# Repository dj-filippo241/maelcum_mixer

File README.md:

# Maelcum Mixer

A one-off, fully analogue, modular dub performance mixer for a 5-way sound system.

Musical decisions and panel layout: Filippo. Engineering (topologies, simulations, PCB generation): Claude, under Filippo's review.

**Status.** Nothing has been built or measured on a bench yet. Every circuit number comes from LTspice simulation or from Python models. The musical behaviour (control laws, saturators, filter character) is being validated by ear on a Max for Live prototype. Component purchases are on hold until that prototype is complete. The PCBs are generated drafts.

## Start here

- **Technical dossier (English):** [`docs/dossier-en/maelcum-mixer-dossier.pdf`](docs/dossier-en/maelcum-mixer-dossier.pdf), also as [HTML](docs/dossier-en/dossier.html). It is the complete English entry point: architecture, every module, numbers and their sources.
- **Block diagrams (English):** [`docs/diagrammi/en/`](docs/diagrammi/en/index.html), starting from [`schema-totale.svg`](docs/diagrammi/en/schema-totale.svg).

The rest of the repository is written in Italian. Technical terms stay in English where they are standard (headroom, summing, feedback, taper).

## Architecture in one paragraph

Four DJ channels (CDJ/line, optional MM phono) with a 4-band isolator EQ and a VCA fader. A shared global filter (HPF and LPF buses after the fader, Xone:96-style law, OTA core with overdrive). A 5-way performance EQ / dub preamp with a kill per band, matching the crossover of the sound system. Four FX buses with a 16-VCA feedback matrix. Mic and generic mono modules. Master, booth and record outputs, CUE, metering in six zones. Design targets: 0 dBu nominal, system headroom of at least +24 dBu (master clips at about +25.5 dBu), no automatic dynamics, nonlinearity only where intended. Simulated system noise: about -83 dBu A-weighted with filters off.

## Repository map

| Path | Content |
|---|---|
| `SPECIFICA.md` | Consolidated specification |
| `docs/01-decisioni-bloccate.md` | Locked decisions, with date and origin |
| `docs/02-questioni-aperte.md` | Open questions |
| `docs/fase1/` ... `docs/fase4/` | Design documents per module |
| `sim/` | LTspice netlists (`.cir`) and results (`RISULTATI-*.md`); shared models in `sim/lib/` |
| `pcb/` | KiCad schematics and 4-layer PCBs, generated by `pcb/<module>/<module>.py` with `pcb/tools/pcbgen.py` |
| `proto-max/` | Max for Live prototype: generators and tests in `proto-max/coefficienti/` |
| `docs/pannelli/` | Panel renders |
| `cheap/` | A parallel low-cost variant, on hold |

Status tags used in the documents: BLOCCATO (locked), PROVVISORIO (provisional), APERTO (open), SUPERATO (superseded, kept as an alternative or as evidence of a dead end).

## Tools

- LTspice 26.0.2, run in batch with `sim/run_ltspice.sh <netlist.cir>`.
- KiCad 10.0.7 with Freerouting; boards are regenerated from their Python script, never edited by hand.
- Max for Live (gen~) for the prototype; the `.genexpr`, `.maxpat` and `.amxd` files are generated.

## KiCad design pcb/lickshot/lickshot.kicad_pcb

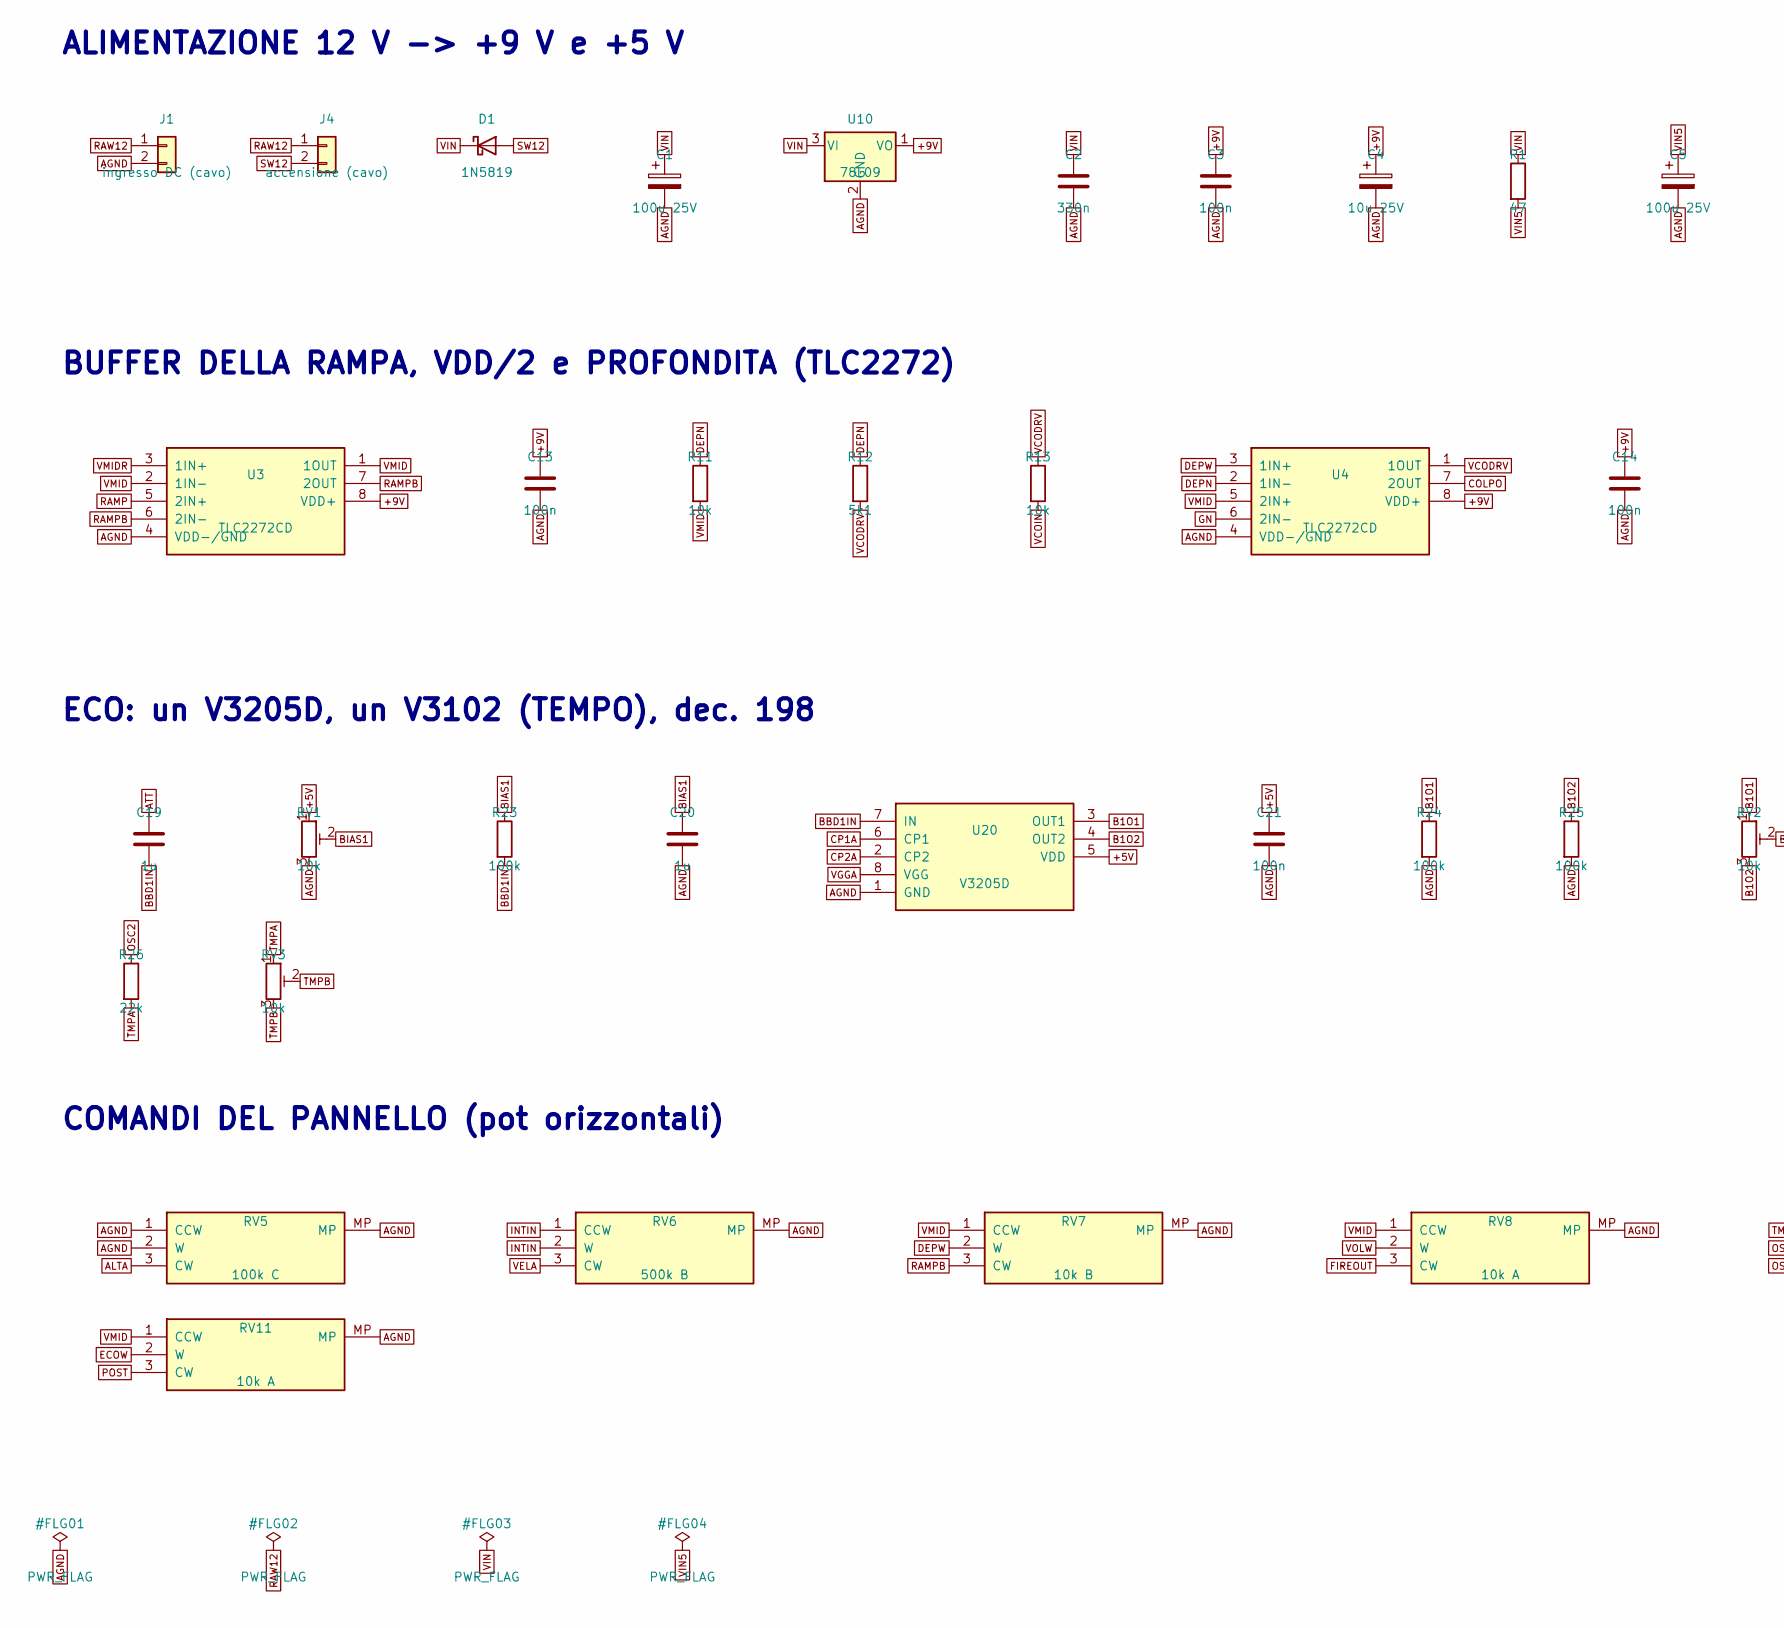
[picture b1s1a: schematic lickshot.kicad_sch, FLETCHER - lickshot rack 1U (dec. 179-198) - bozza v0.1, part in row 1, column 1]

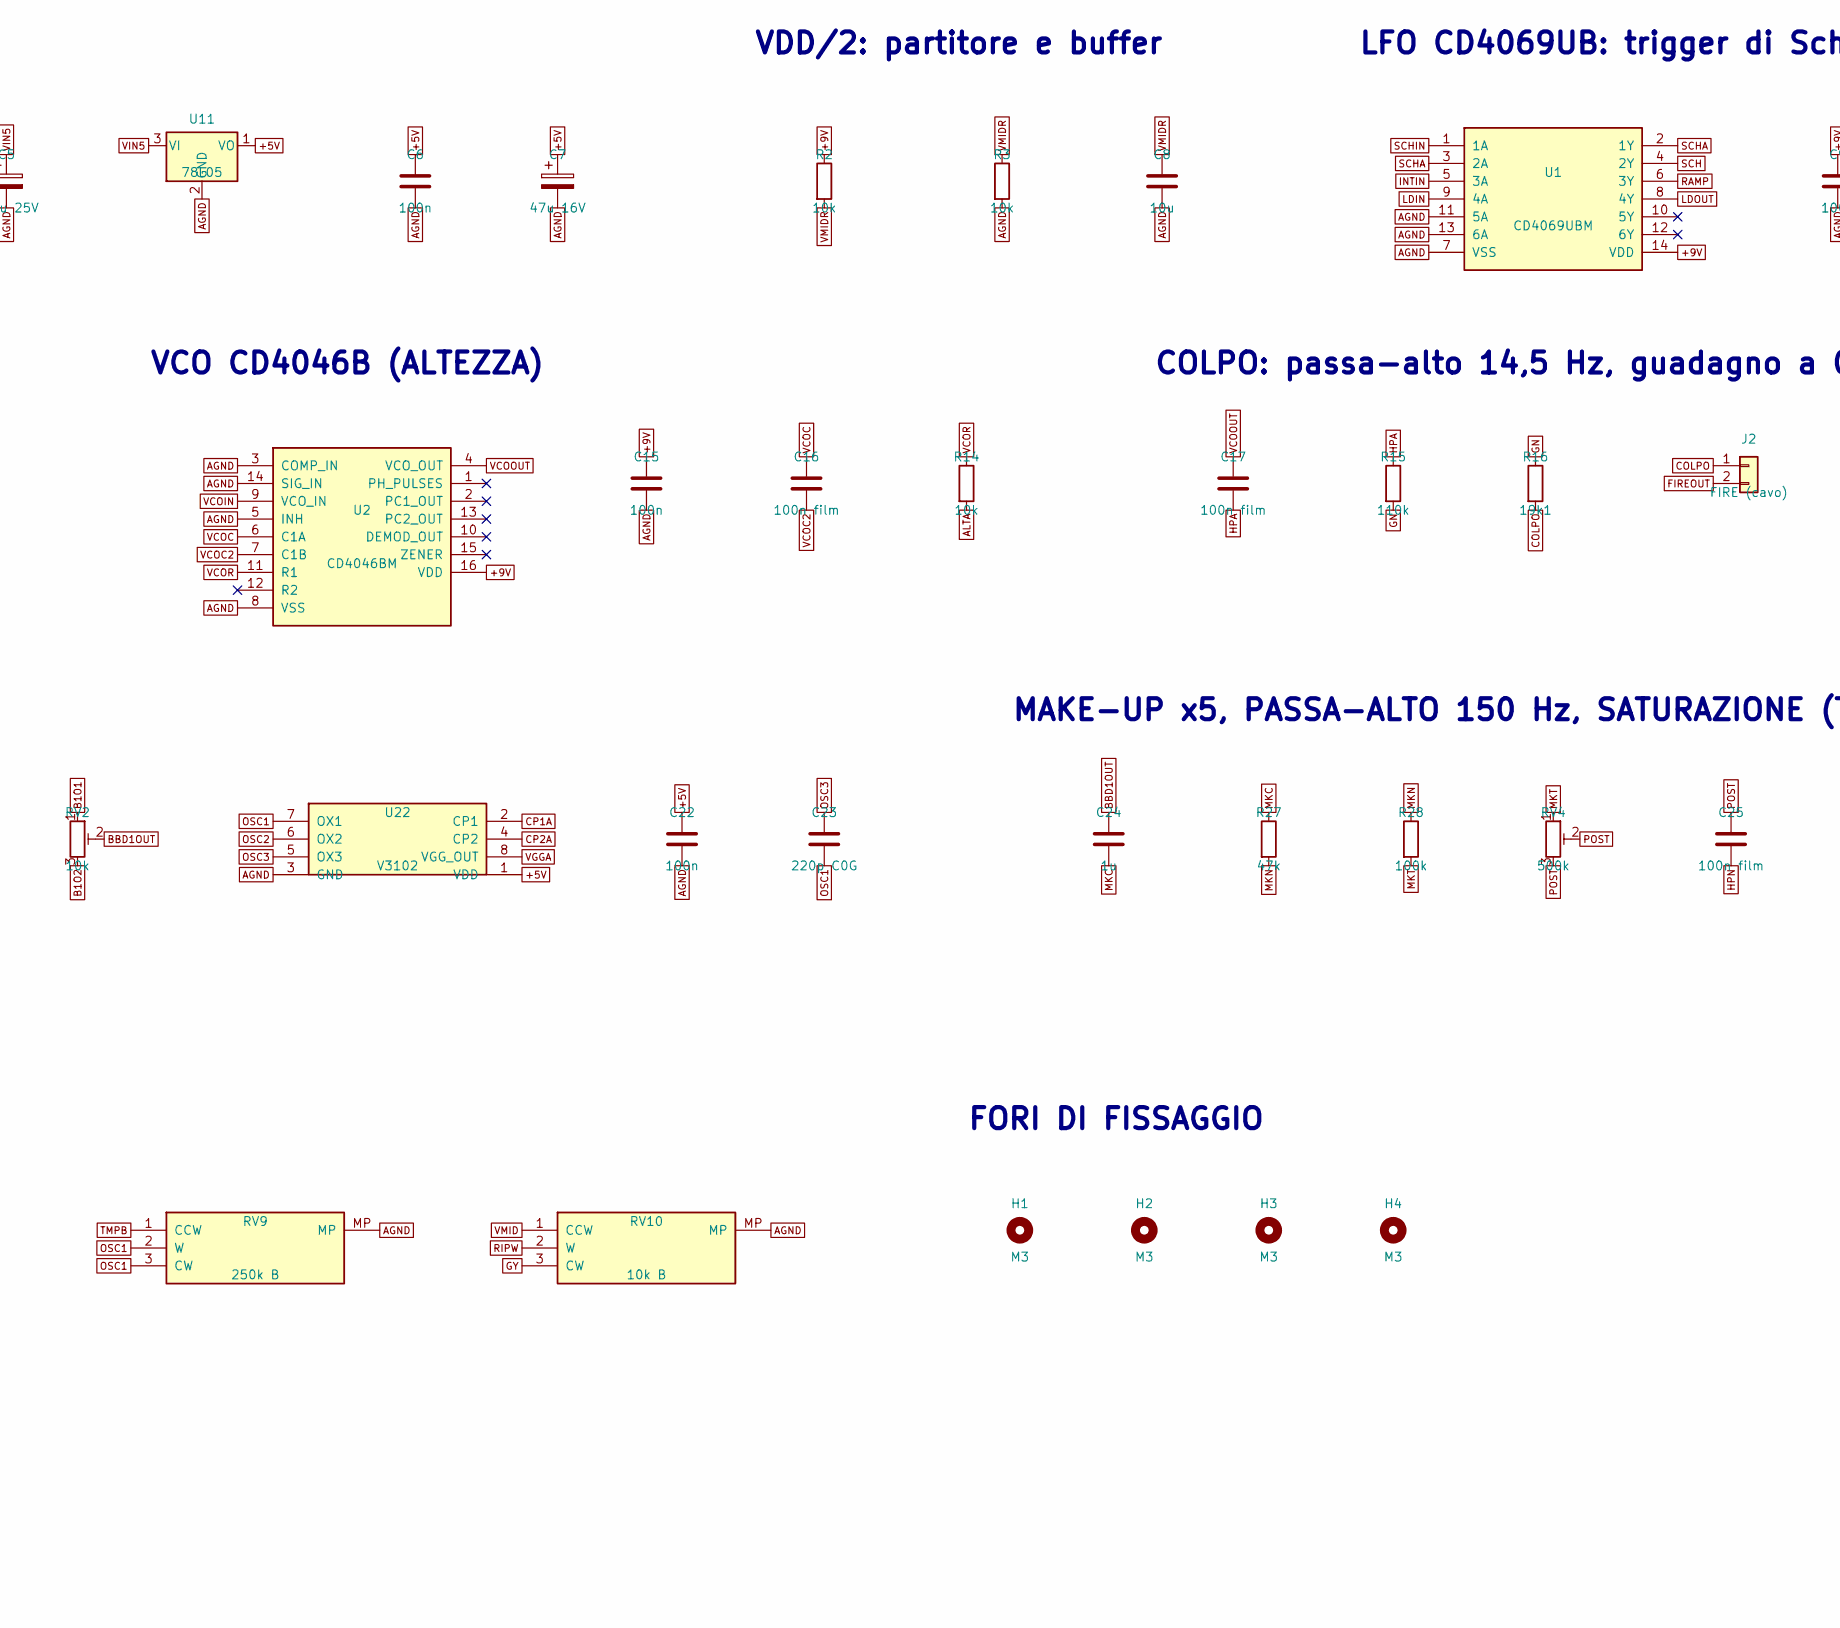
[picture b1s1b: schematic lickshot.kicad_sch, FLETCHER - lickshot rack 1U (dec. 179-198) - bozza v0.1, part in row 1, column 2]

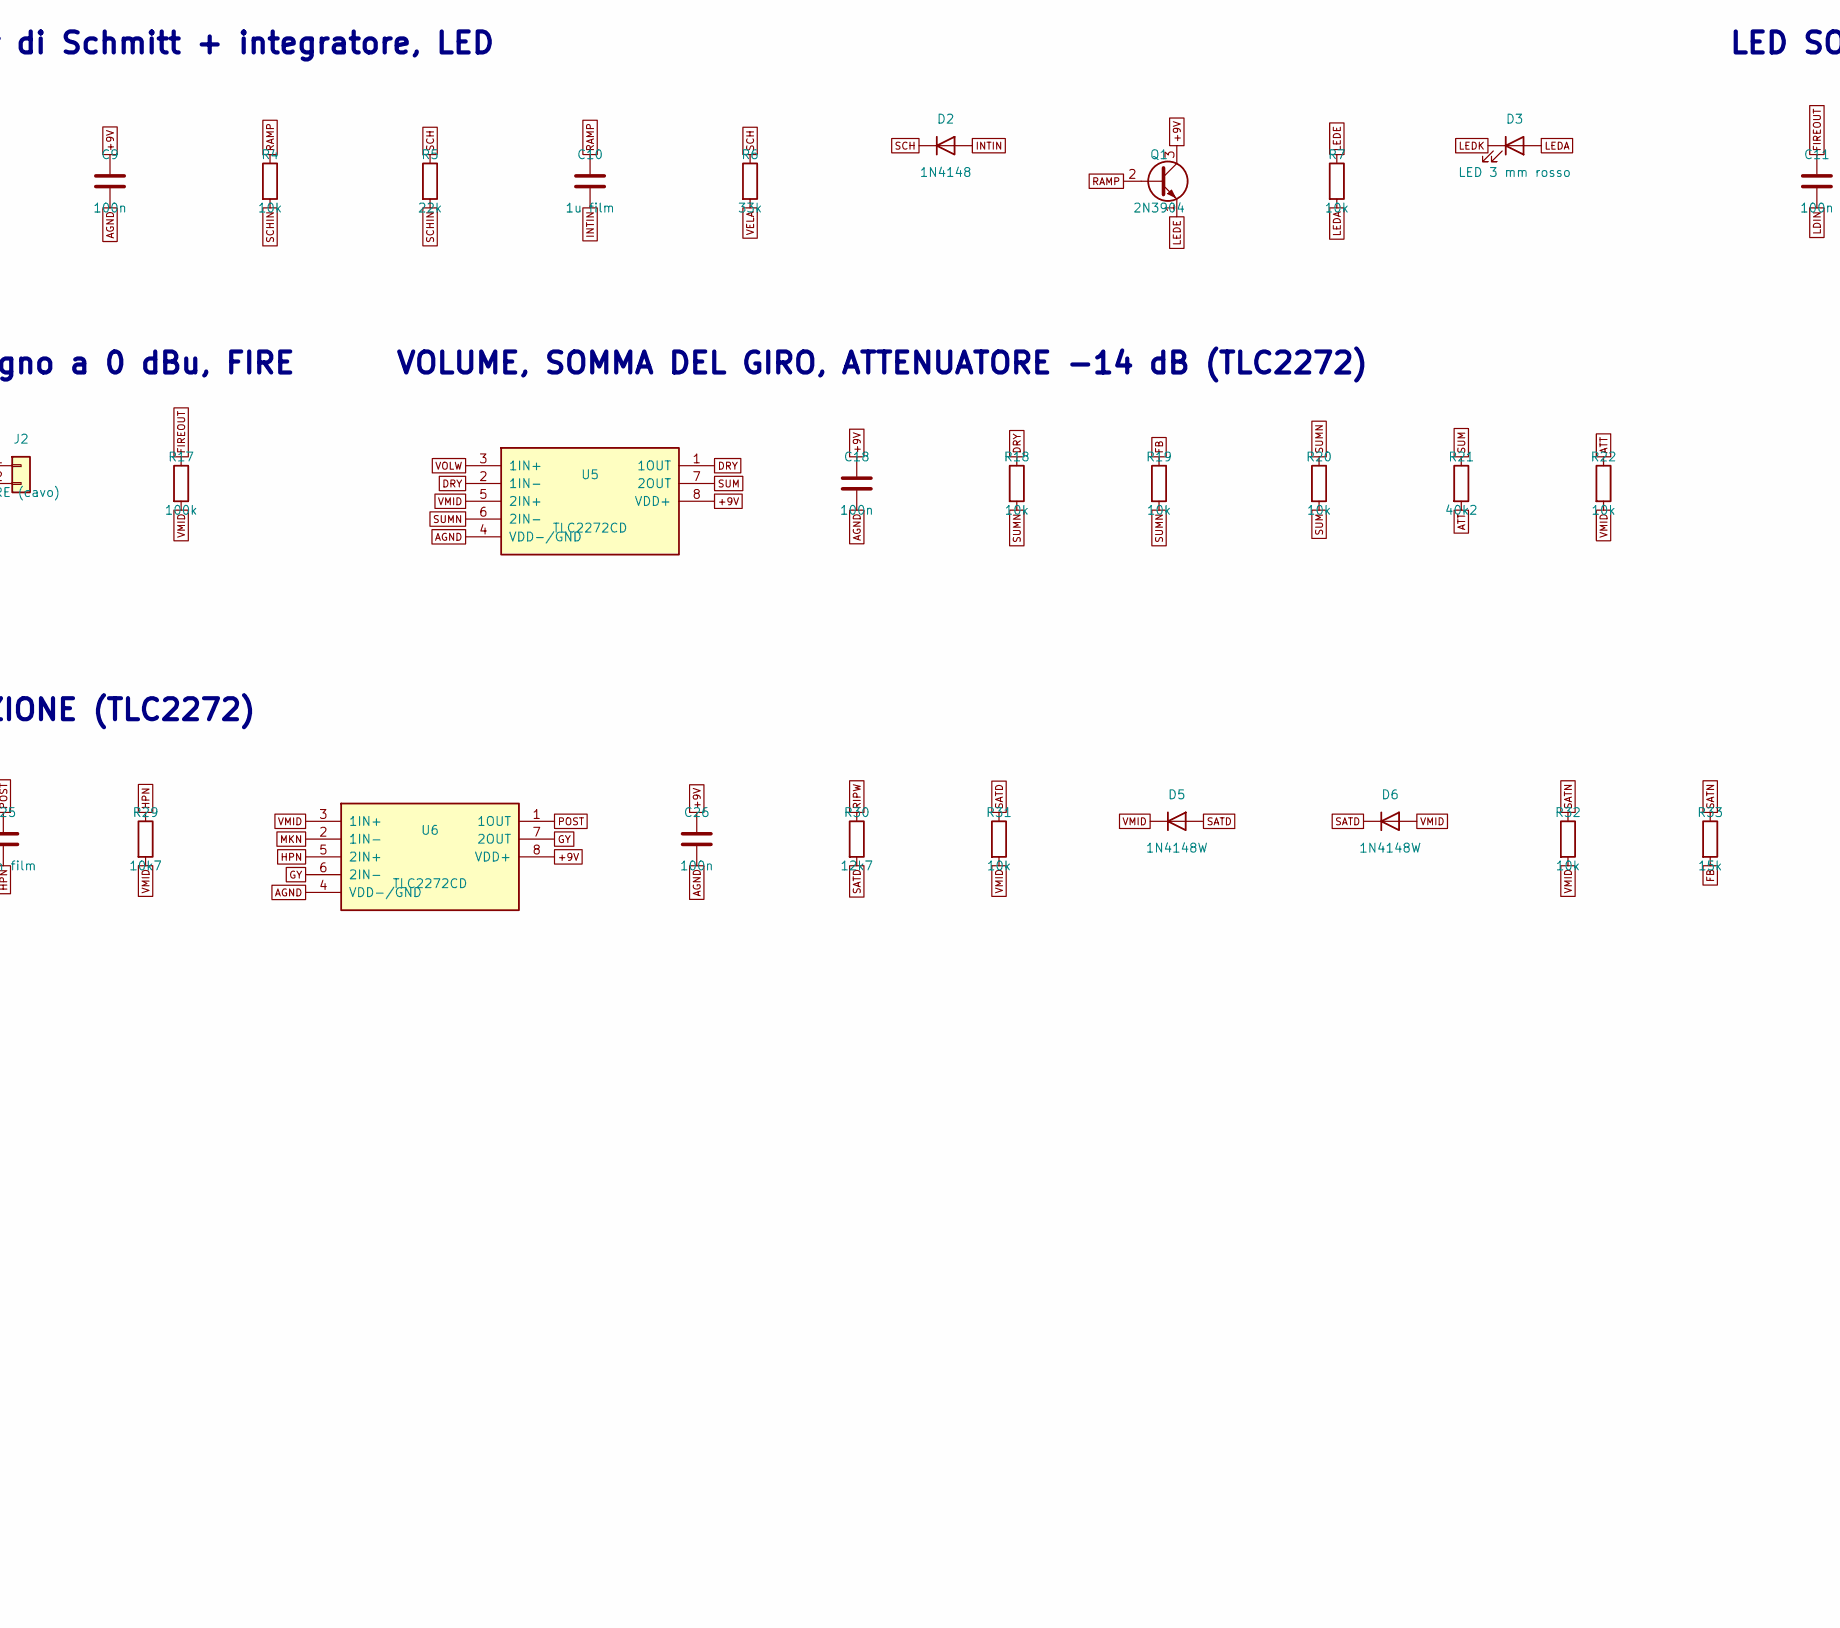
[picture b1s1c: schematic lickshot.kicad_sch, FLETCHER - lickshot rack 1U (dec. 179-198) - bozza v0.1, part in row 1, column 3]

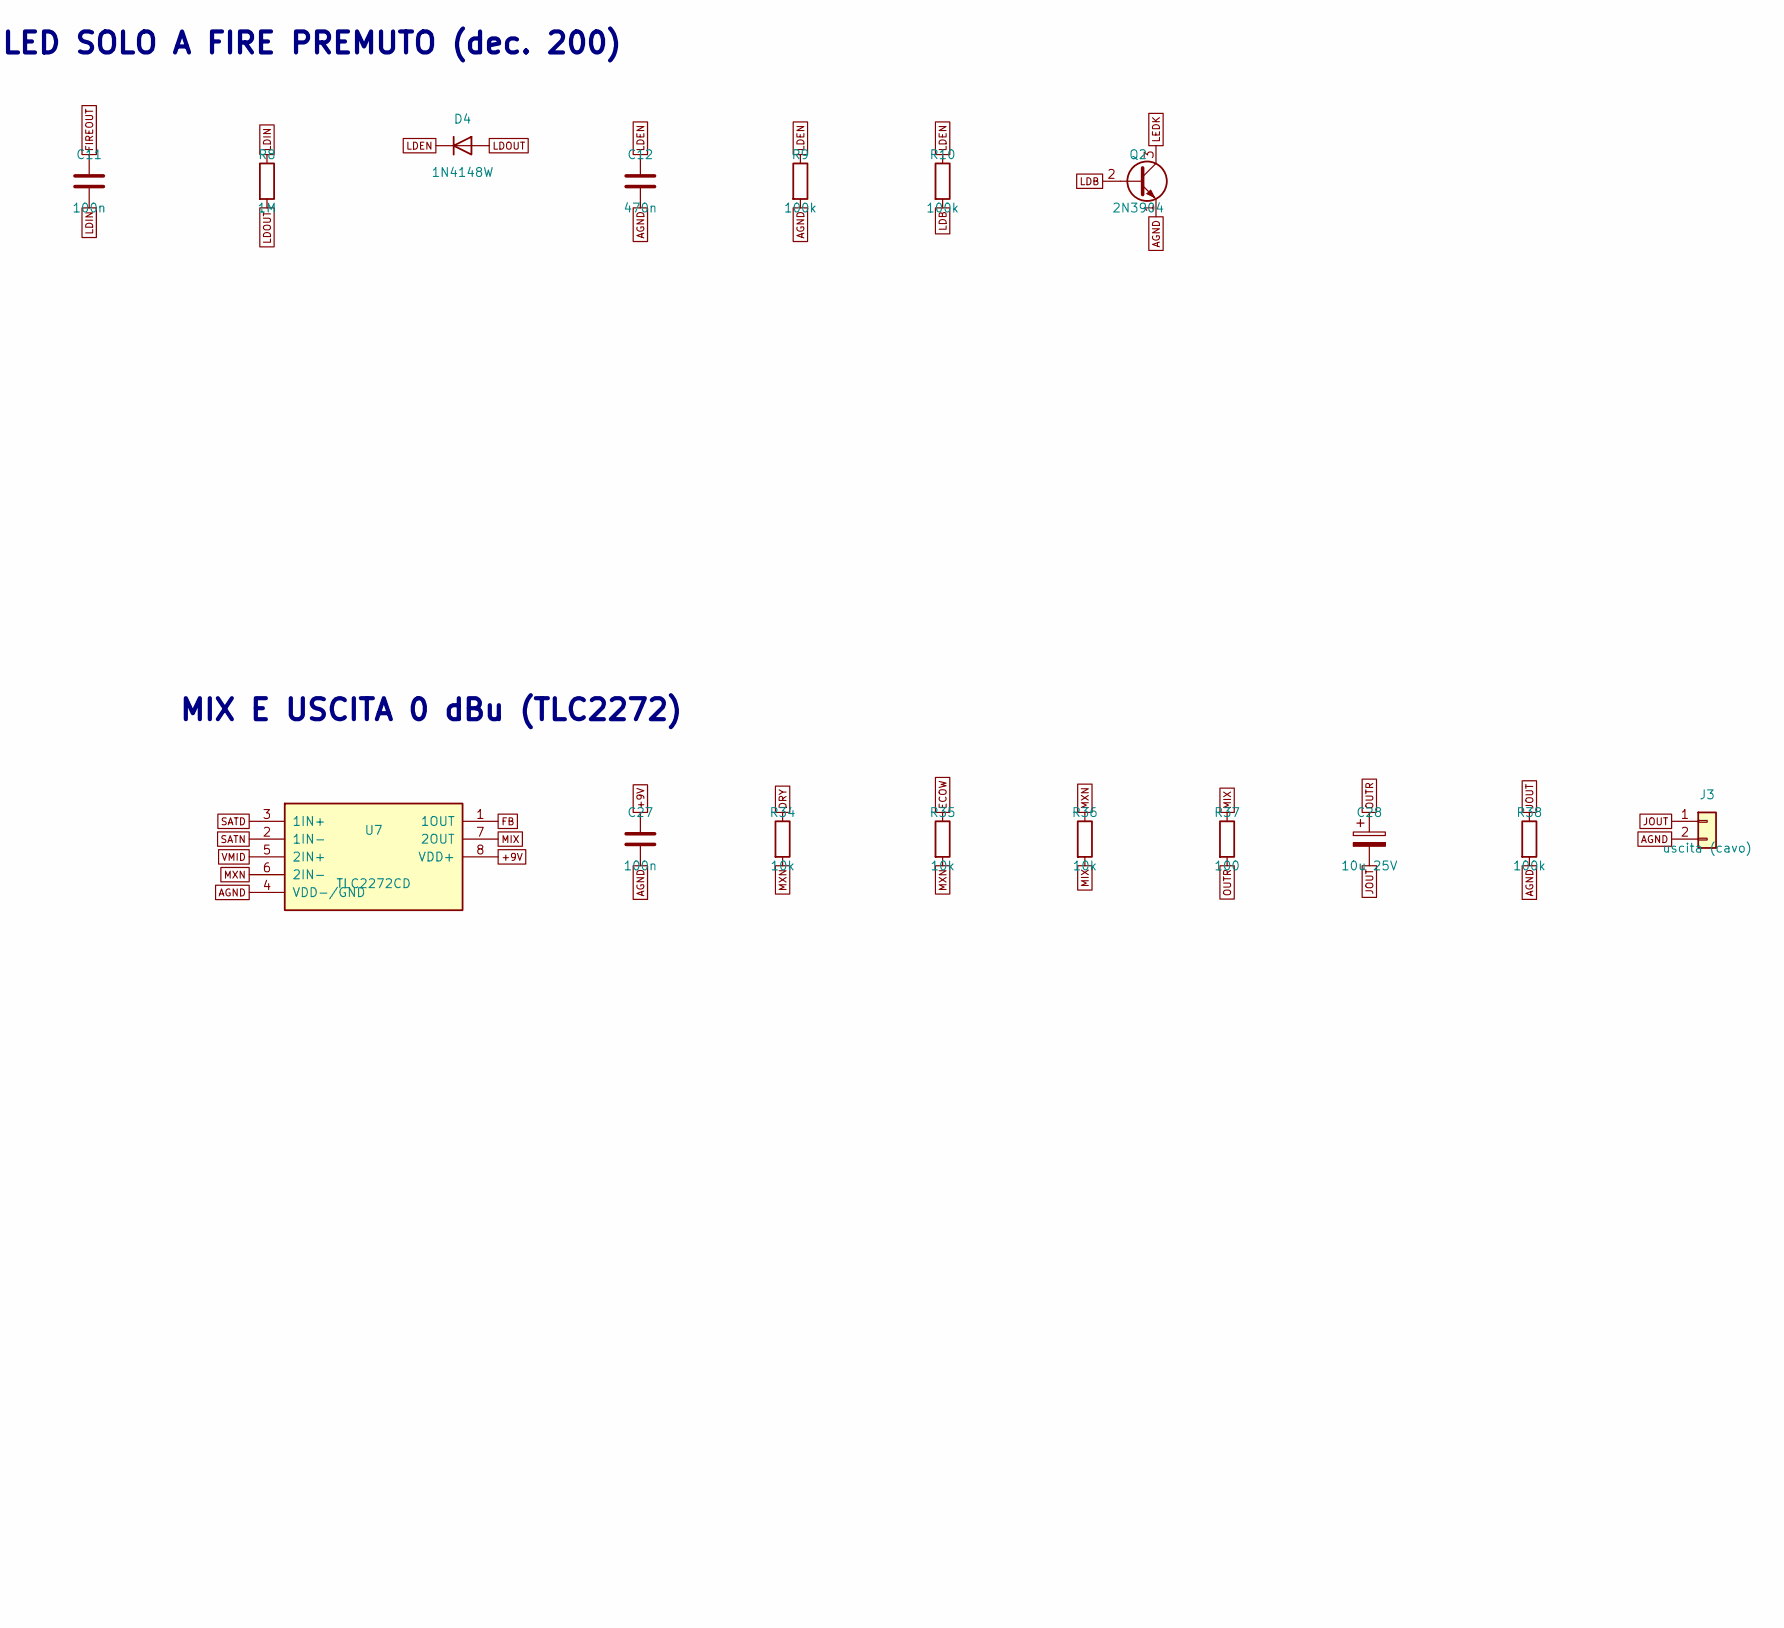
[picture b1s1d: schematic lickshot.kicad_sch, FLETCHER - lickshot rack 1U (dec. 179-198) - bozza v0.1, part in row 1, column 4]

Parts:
C1, C5: 100u 25V; CP_Radial_D8.0mm_P3.50mm
C2: 330n; C_0805_2012Metric
C3, C6, C9, C11, C13, C14, C15, C18, C21, C22, C26, C27: 100n; C_0805_2012Metric
C4, C28: 10u 25V; CP_Radial_D5.0mm_P2.00mm
C7: 47u 16V; CP_Radial_D5.0mm_P2.00mm
C8: 10u; C_1206_3216Metric
C10: 1u film; C_Rect_L7.2mm_W4.5mm_P5.00mm_FKS2_FKP2_MKS2_MKP2
C12: 470n; C_0805_2012Metric
C16, C17, C25: 100n film; C_Rect_L7.2mm_W3.5mm_P5.00mm_FKS2_FKP2_MKS2_MKP2
C19, C20, C24: 1u; C_1206_3216Metric
C23: 220p C0G; C_0805_2012Metric
D1: 1N5819; D_DO-41_SOD81_P10.16mm_Horizontal
D2: 1N4148; D_DO-35_SOD27_P7.62mm_Horizontal
D3: LED 3 mm rosso; LED_D3.0mm_Horizontal_O1.27mm_Z6.0mm
D4, D5, D6: 1N4148W; D_SOD-123
H1, H2, H3, H4: M3; MountingHole_3.2mm_M3
J1: ingresso DC (cavo); PinHeader_1x02_P2.54mm_Vertical
J2: FIRE (cavo); PinHeader_1x02_P2.54mm_Vertical
J3: uscita (cavo); PinHeader_1x02_P2.54mm_Vertical
J4: accensione (cavo); PinHeader_1x02_P2.54mm_Vertical
Q1, Q2: 2N3904; TO-92_Inline_Wide
R1: 47; R_1206_3216Metric
R2, R3, R4, R7, R11, R13, R14, R18, R19, R20, R22, R31, R32, R34, R35, R36: 10k; R_0805_2012Metric
R5, R26: 22k; R_0805_2012Metric
R6: 33k; R_0805_2012Metric
R8: 1M; R_0805_2012Metric
R9, R10, R17, R23, R24, R25, R28, R38: 100k; R_0805_2012Metric
R12: 5k1; R_0805_2012Metric
R15: 110k; R_0805_2012Metric
R16: 19k1; R_0805_2012Metric
R21: 40k2; R_0805_2012Metric
R27: 47k; R_0805_2012Metric
R29: 10k7; R_0805_2012Metric
R30: 12k7; R_0805_2012Metric
R33: 15k; R_0805_2012Metric
R37: 100; R_0805_2012Metric
RV1, RV2, RV3: 10k; Potentiometer_Bourns_3266W_Vertical
RV4: 500k; Potentiometer_Bourns_3224W_Vertical
RV5: 100k C; Potentiometer_Alps_RK09L_Single_Horizontal
RV6: 500k B; Potentiometer_Alps_RK09L_Single_Horizontal
RV7, RV10: 10k B; Potentiometer_Alps_RK09L_Single_Horizontal
RV8, RV11: 10k A; Potentiometer_Alps_RK09L_Single_Horizontal
RV9: 250k B; Potentiometer_Alps_RK09L_Single_Horizontal
U1: CD4069UBM; SOIC-14_3.9x8.7mm_P1.27mm
U2: CD4046BM; SOIC-16_3.9x9.9mm_P1.27mm
U3, U4, U5, U6, U7: TLC2272CD; SOIC-8_3.9x4.9mm_P1.27mm
U10: 78L09; TO-92_Inline_Wide
U11: 78L05; TO-92_Inline_Wide
U20: V3205D; DIP-8_W7.62mm
U22: V3102; DIP-8_W7.62mm

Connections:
+5V: C6.1, C7.1, C21.1, C22.1, RV1.1, U11.1 (VO), U20.5 (VDD), U22.1 (VDD)
+9V: C3.1, C4.1, C9.1, C13.1, C14.1, C15.1, C18.1, C26.1, C27.1, Q1.3 (C), R2.1, U1.14 (VDD), U2.16 (VDD), U3.8 (VDD+), U4.8 (VDD+), U5.8 (VDD+), U6.8 (VDD+), U7.8 (VDD+), U10.1 (VO)
AGND: C1.2, C2.2, C3.2, C4.2, C5.2, C6.2, C7.2, C8.2, C9.2, C12.2, C13.2, C14.2, C15.2, C18.2, C20.2, C21.2, C22.2, C26.2, C27.2, J1.2, J3.2, Q2.1 (E), R3.2, R9.2, R24.2, R25.2, R38.2, RV1.3, RV5.1 (CCW), RV5.2 (W), RV5.MP, RV6.MP, RV7.MP, RV8.MP, RV9.MP, RV10.MP, RV11.MP, U1.7 (VSS), U1.11 (5A), U1.13 (6A), U2.3 (COMP_IN), U2.5 (INH), U2.8 (VSS), U2.14 (SIG_IN), U3.4 (VDD-/GND), U4.4 (VDD-/GND), U5.4 (VDD-/GND), U6.4 (VDD-/GND), U7.4 (VDD-/GND), U10.2 (GND), U11.2 (GND), U20.1 (GND), U22.3 (GND)
ALTA: R14.2, RV5.3 (CW)
ATT: C19.1, R21.2, R22.1
B1O1: R24.1, RV2.1, U20.3 (OUT1)
B1O2: R25.1, RV2.3, U20.4 (OUT2)
BBD1IN: C19.2, R23.2, U20.7 (IN)
BBD1OUT: C24.1, RV2.2
BIAS1: C20.1, R23.1, RV1.2
COLPO: J2.1, R16.2, U4.7 (2OUT)
CP1A: U20.6 (CP1), U22.2 (CP1)
CP2A: U20.2 (CP2), U22.4 (CP2)
DEPN: R11.1, R12.1, U4.2 (1IN-)
DEPW: RV7.2 (W), U4.3 (1IN+)
DRY: R18.1, R34.1, U5.1 (1OUT), U5.2 (1IN-)
ECOW: R35.1, RV11.2 (W)
FB: R19.1, R33.2, U7.1 (1OUT)
FIREOUT: C11.1, J2.2, R17.1, RV8.3 (CW)
GN: R15.2, R16.1, U4.6 (2IN-)
GY: RV10.3 (CW), U6.6 (2IN-), U6.7 (2OUT)
HPA: C17.2, R15.1
HPN: C25.2, R29.1, U6.5 (2IN+)
INTIN: C10.2, D2.2 (A), RV6.1 (CCW), RV6.2 (W), U1.5 (3A)
JOUT: C28.2, J3.1, R38.1
LDB: Q2.2 (B), R10.2
LDEN: C12.1, D4.1 (K), R9.1, R10.1
LDIN: C11.2, R8.1, U1.9 (4A)
LDOUT: D4.2 (A), R8.2, U1.8 (4Y)
LEDA: D3.2 (A), R7.2
LEDE: Q1.1 (E), R7.1
LEDK: D3.1 (K), Q2.3 (C)
MIX: R36.2, R37.1, U7.7 (2OUT)
MKC: C24.2, R27.1
MKN: R27.2, R28.1, U6.2 (1IN-)
MKT: R28.2, RV4.1
MXN: R34.2, R35.2, R36.1, U7.6 (2IN-)
OSC1: C23.2, RV9.2 (W), RV9.3 (CW), U22.7 (OX1)
OSC2: R26.1, U22.6 (OX2)
OSC3: C23.1, U22.5 (OX3)
OUTR: C28.1, R37.2
POST: C25.1, RV4.2, RV4.3, RV11.3 (CW), U6.1 (1OUT)
RAMP: C10.1, Q1.2 (B), R4.1, U1.6 (3Y), U3.5 (2IN+)
RAMPB: RV7.3 (CW), U3.6 (2IN-), U3.7 (2OUT)
RAW12: J1.1, J4.1
RIPW: R30.1, RV10.2 (W)
SATD: D5.2 (A), D6.1 (K), R30.2, R31.1, U7.3 (1IN+)
SATN: R32.1, R33.1, U7.2 (1IN-)
SCH: D2.1 (K), R5.1, R6.1, U1.4 (2Y)
SCHA: U1.2 (1Y), U1.3 (2A)
SCHIN: R4.2, R5.2, U1.1 (1A)
SUM: R20.2, R21.1, U5.7 (2OUT)
SUMN: R18.2, R19.2, R20.1, U5.6 (2IN-)
SW12: D1.2 (A), J4.2
TMPA: R26.2, RV3.1
TMPB: RV3.2, RV3.3, RV9.1 (CCW)
VCOC: C16.1, U2.6 (C1A)
VCOC2: C16.2, U2.7 (C1B)
VCODRV: R12.2, R13.1, U4.1 (1OUT)
VCOIN: R13.2, U2.9 (VCO_IN)
VCOOUT: C17.1, U2.4 (VCO_OUT)
VCOR: R14.1, U2.11 (R1)
VELA: R6.2, RV6.3 (CW)
VGGA: U20.8 (VGG), U22.8 (VGG_OUT)
VIN: C1.1, C2.1, D1.1 (K), R1.1, U10.3 (VI)
VIN5: C5.1, R1.2, U11.3 (VI)
VMID: D5.1 (K), D6.2 (A), R11.2, R17.2, R22.2, R29.2, R31.2, R32.2, RV7.1 (CCW), RV8.1 (CCW), RV10.1 (CCW), RV11.1 (CCW), U3.1 (1OUT), U3.2 (1IN-), U4.5 (2IN+), U5.5 (2IN+), U6.3 (1IN+), U7.5 (2IN+)
VMIDR: C8.1, R2.2, R3.1, U3.3 (1IN+)
VOLW: RV8.2 (W), U5.3 (1IN+)

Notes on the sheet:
ALIMENTAZIONE 12 V -> +9 V e +5 V
VDD/2: partitore e buffer
LFO CD4069UB: trigger di Schmitt + integratore, LED
LED SOLO A FIRE PREMUTO (dec. 200)
BUFFER DELLA RAMPA, VDD/2 e PROFONDITA (TLC2272)
VCO CD4046B (ALTEZZA)
COLPO: passa-alto 14,5 Hz, guadagno a 0 dBu, FIRE
VOLUME, SOMMA DEL GIRO, ATTENUATORE -14 dB (TLC2272)
ECO: un V3205D, un V3102 (TEMPO), dec. 198
MAKE-UP x5, PASSA-ALTO 150 Hz, SATURAZIONE (TLC2272)
MIX E USCITA 0 dBu (TLC2272)
COMANDI DEL PANNELLO (pot orizzontali)
FORI DI FISSAGGIO

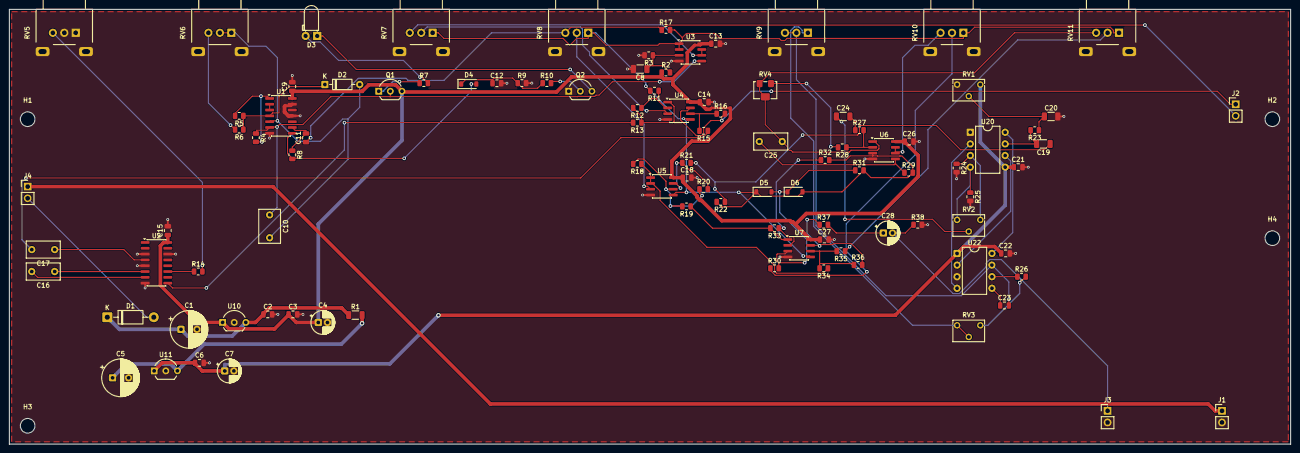
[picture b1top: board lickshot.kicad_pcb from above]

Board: 4 copper layers, 280.0 x 95.0 mm, 104 parts (0 on the bottom side), 69 nets.
